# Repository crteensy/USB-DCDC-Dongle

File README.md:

# USB-DCDC-Dongle
A simple USB dongle that hosts a DCDC converter to get +/- 5V from USB

BOM:
- Isolated DCDC converter, SIP-7 with 5 pins
- 2 SOT-523 Schottky Diodes
- CUI_DEVICES_SJ-43514-SMT-TR 4-pin Audio jack
- JST XH S3B-XH-A header

PCB
- 2 layers
- must be 2 mm thick for a better fit in the USB slot. 1.6 mm does work, but falls out easily especially if the slot has seen a lot of use before.
- ENIG finish (and optionally hard gold for the USB contacts)

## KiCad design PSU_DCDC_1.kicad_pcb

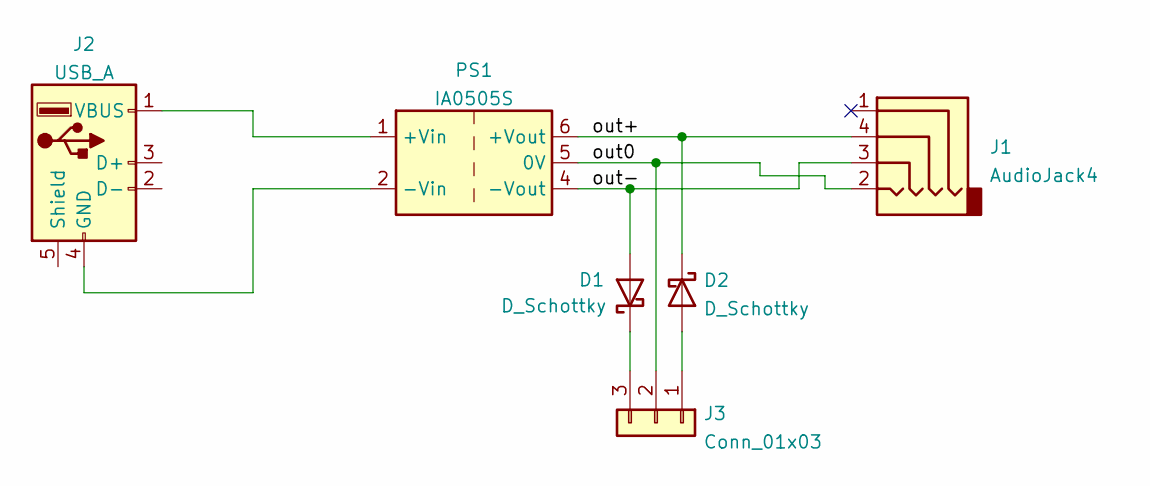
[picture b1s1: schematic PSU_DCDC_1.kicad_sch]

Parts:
D1, D2: D_Schottky; D_SOD-523
J1: AudioJack4; SJ-43514-SMT
J2: USB_A; USB_A_PCB_Traces_crteensy
J3: Conn_01x03; JST_XH_S3B-XH-A_1x03_P2.50mm_Horizontal
PS1: IA0505S; Converter_DCDC_TRACO_TMR-1-xxxx_Dual_THT

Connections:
/out0: J1.2, J3.2, PS1.5 (0V)
/out+: D2.1 (K), J1.4, PS1.6 (+Vout)
/out-: D1.2 (A), J1.3, PS1.4 (-Vout)
unnamed: D1.1 (K), J3.3
unnamed: D2.2 (A), J3.1
unnamed: J2.1 (VBUS), PS1.1 (+Vin)
unnamed: J2.4 (GND), PS1.2 (-Vin)

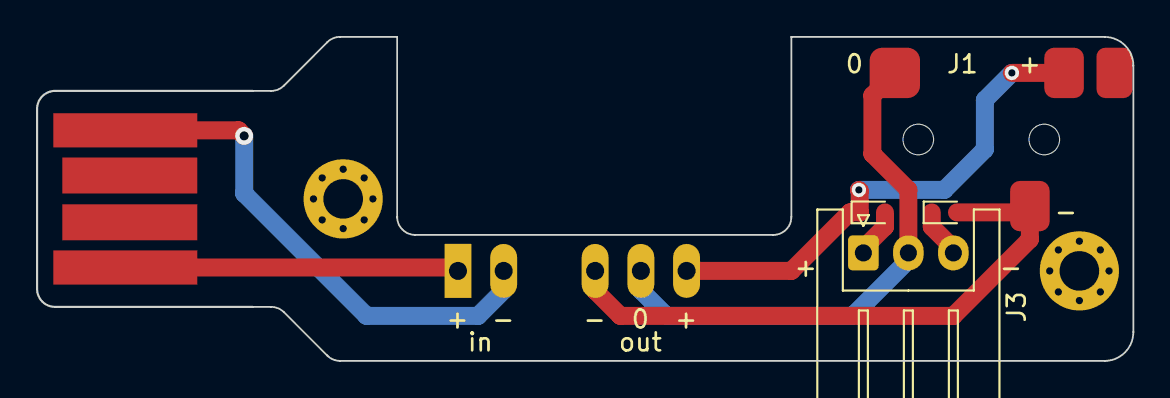
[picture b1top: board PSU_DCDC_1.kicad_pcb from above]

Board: 2 copper layers, 60.9 x 18.0 mm, 6 parts (1 on the bottom side), 7 nets.
